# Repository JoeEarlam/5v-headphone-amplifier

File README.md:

# 5v-headphone-amplifier

A small, op-amp based headphone amplifier with a BOM cost of under £10 - think CMOY on steroids. Designed to run from 5V power, specifically cheap single-cell USB powerbanks, where it can be stuck to the side with velcro or double sided tape.

Uses an RC4580D, but any standard footprint SOIC-8 op-amp can be substituted.

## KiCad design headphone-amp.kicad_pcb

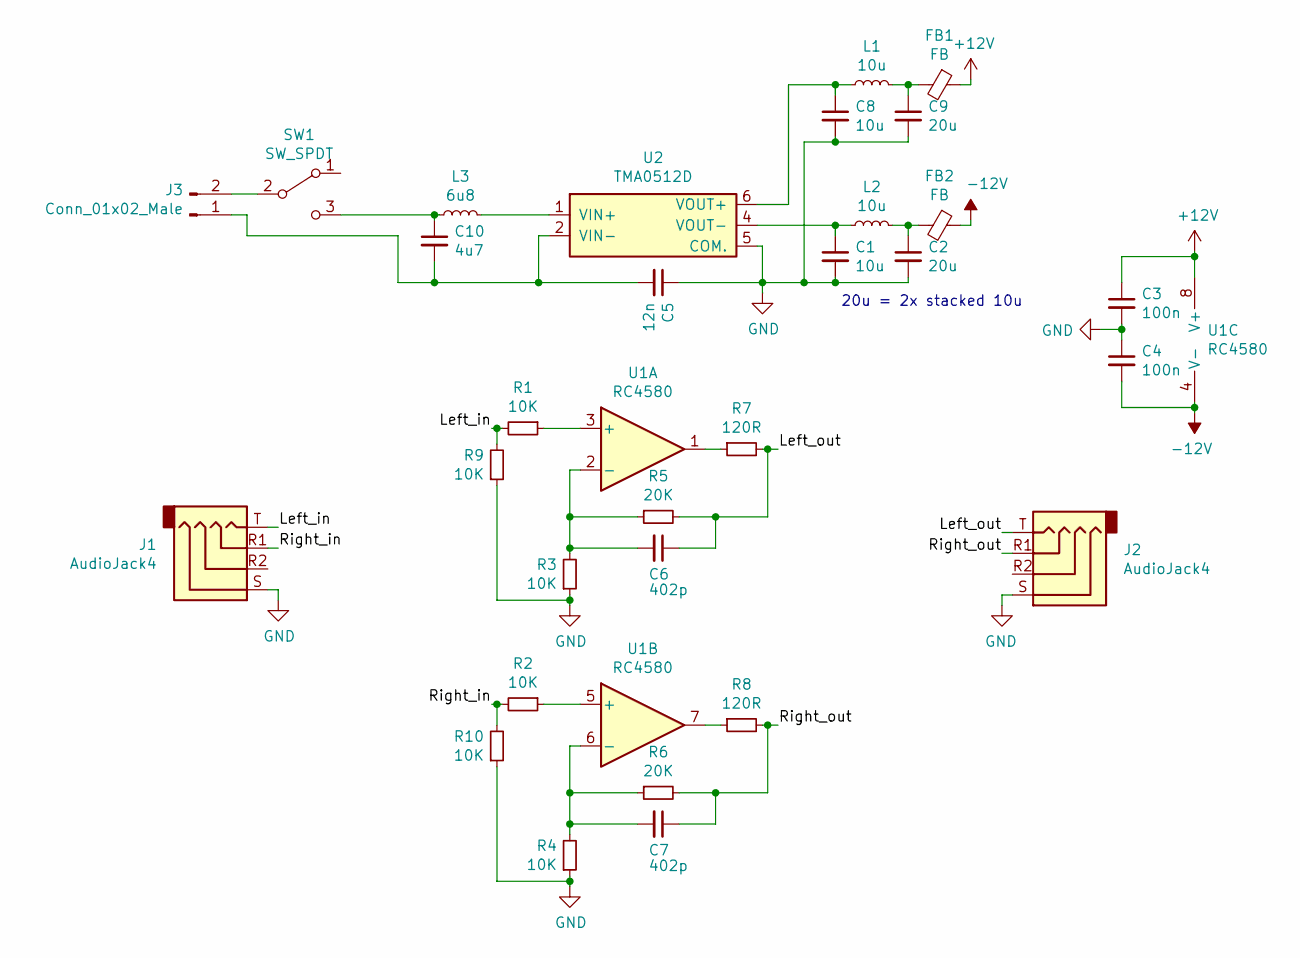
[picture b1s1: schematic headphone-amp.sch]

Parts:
C1, C8: 10u; C_0805_2012Metric
C2, C9: 20u; C_0805_2012Metric
C3, C4: 100n; C_0805_2012Metric
C5: 12n; C_0805_2012Metric
C6, C7: 402p; C_0805_2012Metric
C10: 4u7; C_0805_2012Metric
FB1, FB2: FB; L_0805_2012Metric
J1, J2: AudioJack4; Jack_3.5mm_PJ320D_Horizontal
J3: Conn_01x02_Male; JST_PH_S2B-PH-SM4-TB_1x02-1MP_P2.00mm_Horizontal
L1, L2: 10u; L_0805_2012Metric
L3: 6u8; L_0805_2012Metric
R1, R2, R3, R4, R9, R10: 10K; R_0805_2012Metric
R5, R6: 20K; R_0805_2012Metric
R7, R8: 120R; R_0805_2012Metric
SW1: SW_SPDT; SW_SPDT_CK-JS102011SAQN
U1: RC4580; SOIC-8_3.9x4.9mm_P1.27mm
U2: TMA0512D; TMAxxxxD_horizontal

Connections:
+12V: C3.1, FB1.1, U1.8 (V+)
-12V: C4.2, FB2.1, U1.4 (V-)
/Left_in: J1.T, R1.2, R9.2
/Left_out: C6.1, J2.T, R5.2, R7.2
/Right_in: J1.R1, R2.2, R10.2
/Right_out: C7.1, J2.R1, R6.2, R8.2
GND: C1.2, C2.2, C3.2, C4.1, C5.1, C8.2, C9.2, J1.S, J2.S, R3.1, R4.1, R9.1, R10.1, U2.5 (COM.)
unnamed: C1.1, L2.1, U2.4 (VOUT-)
unnamed: C2.1, FB2.2, L2.2
unnamed: C6.2, R3.2, R5.1, U1.2 (-)
unnamed: C7.2, R4.2, R6.1, U1.6 (-)
unnamed: C8.1, L1.1, U2.6 (VOUT+)
unnamed: C9.1, FB1.2, L1.2
unnamed: C10.1, L3.1, SW1.3 (C)
unnamed: C5.2, C10.2, J3.1, U2.2 (VIN-)
unnamed: J3.2, SW1.2 (B)
unnamed: L3.2, U2.1 (VIN+)
unnamed: R1.1, U1.3 (+)
unnamed: R2.1, U1.5 (+)
unnamed: R7.1, U1.1
unnamed: R8.1, U1.7

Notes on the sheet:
20u = 2x stacked 10u

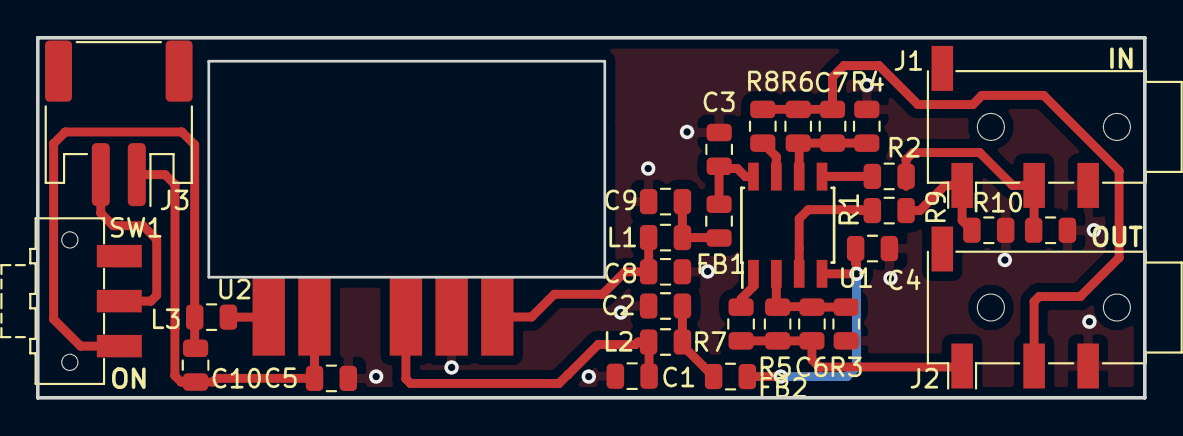
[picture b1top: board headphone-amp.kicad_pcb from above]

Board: 2 copper layers, 61.5 x 20.0 mm, 31 parts (0 on the bottom side), 21 nets.

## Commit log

2019-02-06 changed feedback networks slightly
2019-02-07 tag for prototype production
2019-02-07 changed filtering network
2019-02-10 as sent to production
2019-02-12 minor changes to filtering networks
2019-02-12 added input filtering to DC-DC converter
2019-02-13 Added input resistors
